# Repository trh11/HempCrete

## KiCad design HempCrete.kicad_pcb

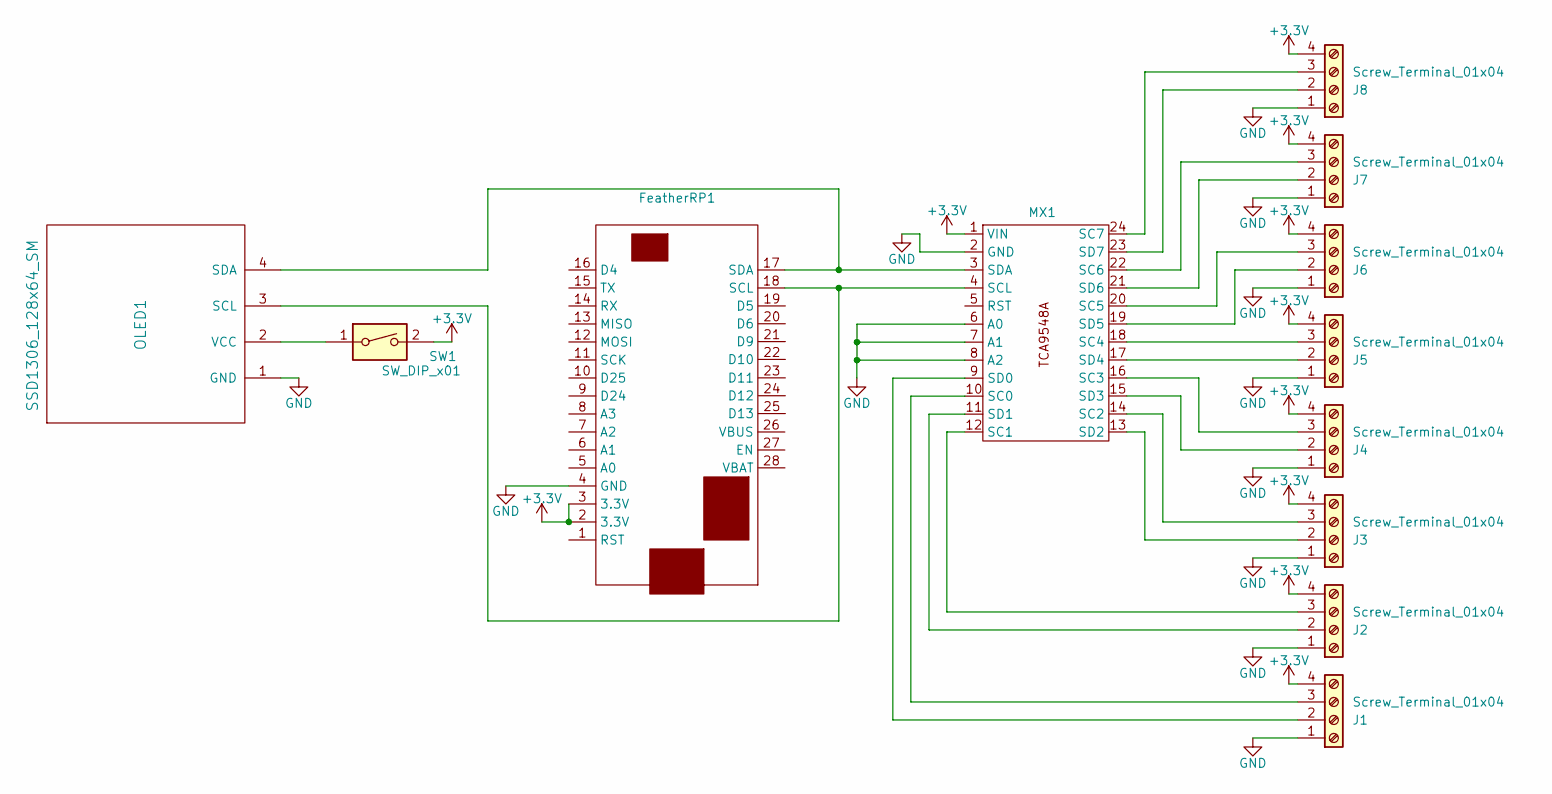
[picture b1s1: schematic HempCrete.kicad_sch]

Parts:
FeatherRP1: Feather RP2040
J1, J2, J3, J4, J5, J6, J7, J8: Screw_Terminal_01x04; PinHeader_1x04_P2.54mm_Vertical
MX1: TCA9548A
OLED1: SSD1306_128x64_SM; SSD1306_128x64
SW1: SW_DIP_x01; PinHeader_1x03_P2.54mm_Vertical

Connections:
+3.3V: FeatherRP1.2 (3.3V), FeatherRP1.3 (3.3V), J1.4, J2.4, J3.4, J4.4, J5.4, J6.4, J7.4, J8.4, MX1.1 (VIN), SW1.2
GND: FeatherRP1.4 (GND), J1.1, J2.1, J3.1, J4.1, J5.1, J6.1, J7.1, J8.1, MX1.2 (GND), MX1.6 (A0), MX1.7 (A1), MX1.8 (A2), OLED1.1 (GND)
unnamed: FeatherRP1.18 (SCL), MX1.4 (SCL), OLED1.3 (SCL)
unnamed: FeatherRP1.17 (SDA), MX1.3 (SDA), OLED1.4 (SDA)
unnamed: J1.2, MX1.9 (SD0)
unnamed: J1.3, MX1.10 (SC0)
unnamed: J2.2, MX1.11 (SD1)
unnamed: J2.3, MX1.12 (SC1)
unnamed: J3.2, MX1.13 (SD2)
unnamed: J3.3, MX1.14 (SC2)
unnamed: J4.2, MX1.15 (SD3)
unnamed: J4.3, MX1.16 (SC3)
unnamed: J5.2, MX1.17 (SD4)
unnamed: J5.3, MX1.18 (SC4)
unnamed: J6.2, MX1.19 (SD5)
unnamed: J6.3, MX1.20 (SC5)
unnamed: J7.2, MX1.21 (SD6)
unnamed: J7.3, MX1.22 (SC6)
unnamed: J8.2, MX1.23 (SD7)
unnamed: J8.3, MX1.24 (SC7)
unnamed: OLED1.2 (VCC), SW1.1

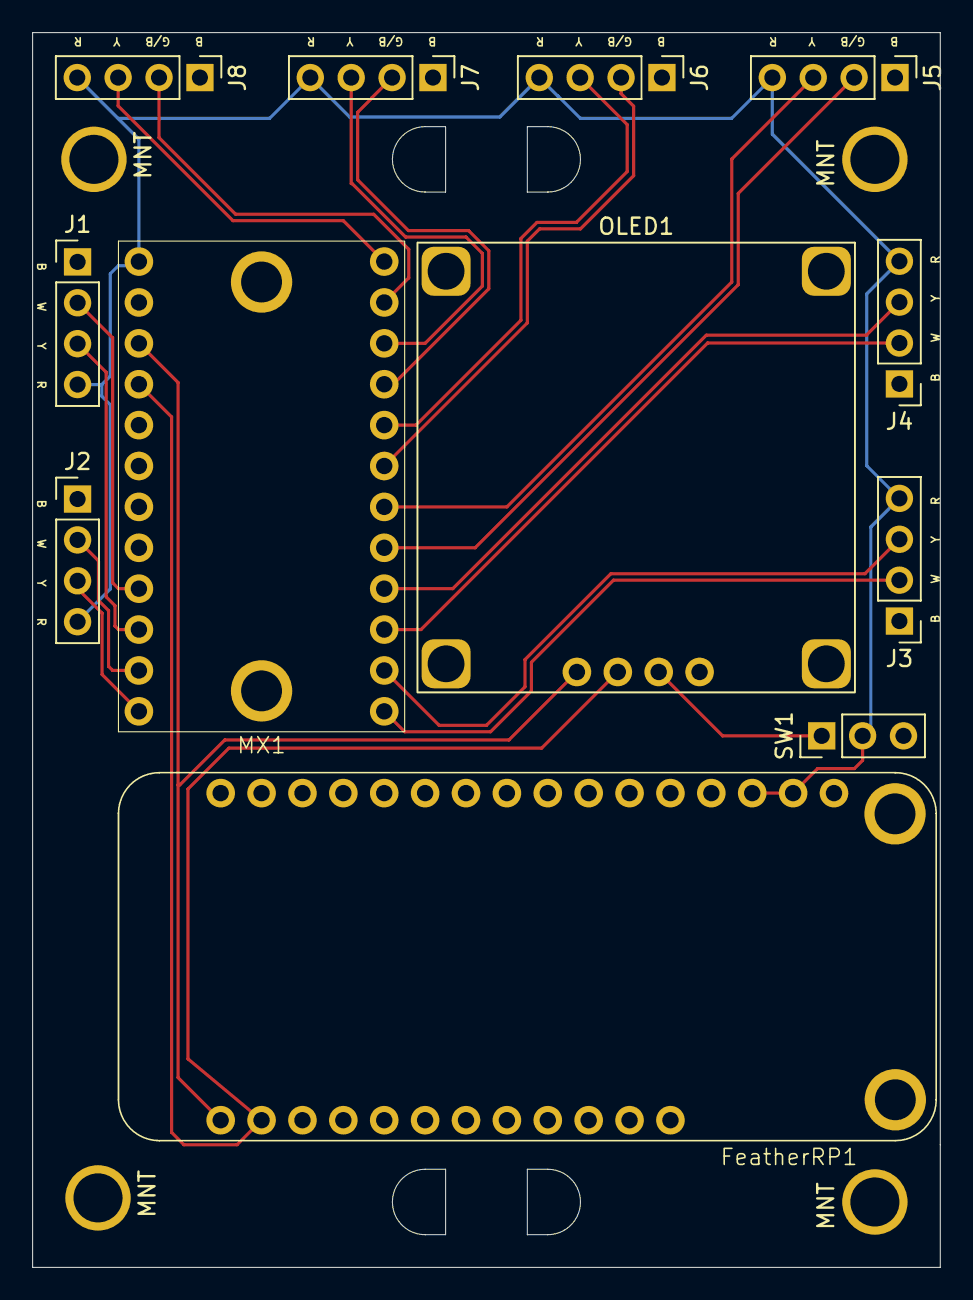
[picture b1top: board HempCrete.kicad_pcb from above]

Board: 2 copper layers, 56.4 x 76.7 mm, 16 parts (0 on the bottom side), 21 nets.

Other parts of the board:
MNT: 4-40Mount
MNT#2, MNT#3, MNT#4: 4-40Mount

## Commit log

2025-03-05 removing files
2025-03-05 removing files 3
2025-03-05 removing files 4
2025-03-05 removing backup directories
